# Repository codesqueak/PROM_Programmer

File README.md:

# PROM Programmer and Editor

PROM programmere for the following 32 x 8 PROM's

* National  74S188
* Fujitsu   7111
* Signetics 82S23
* AMD       27S18
* MMI       6330
* TI        18SA30
* Harris    7602

## Introduction

This board has been designed to allow the programming and editing of the above PROM's

* Programming timings as per the manufacturers recommendations
* All components are readily available from commercial component suppliers (..and eBay!)
* Copious test points
* Full documentation

For full documentation, see the [pdf here](PROM_Programmer.pdf)

* Yellow – Start
* Pink – Vcc
* Cyan – Programming Pulse
* Green – Chip Enable

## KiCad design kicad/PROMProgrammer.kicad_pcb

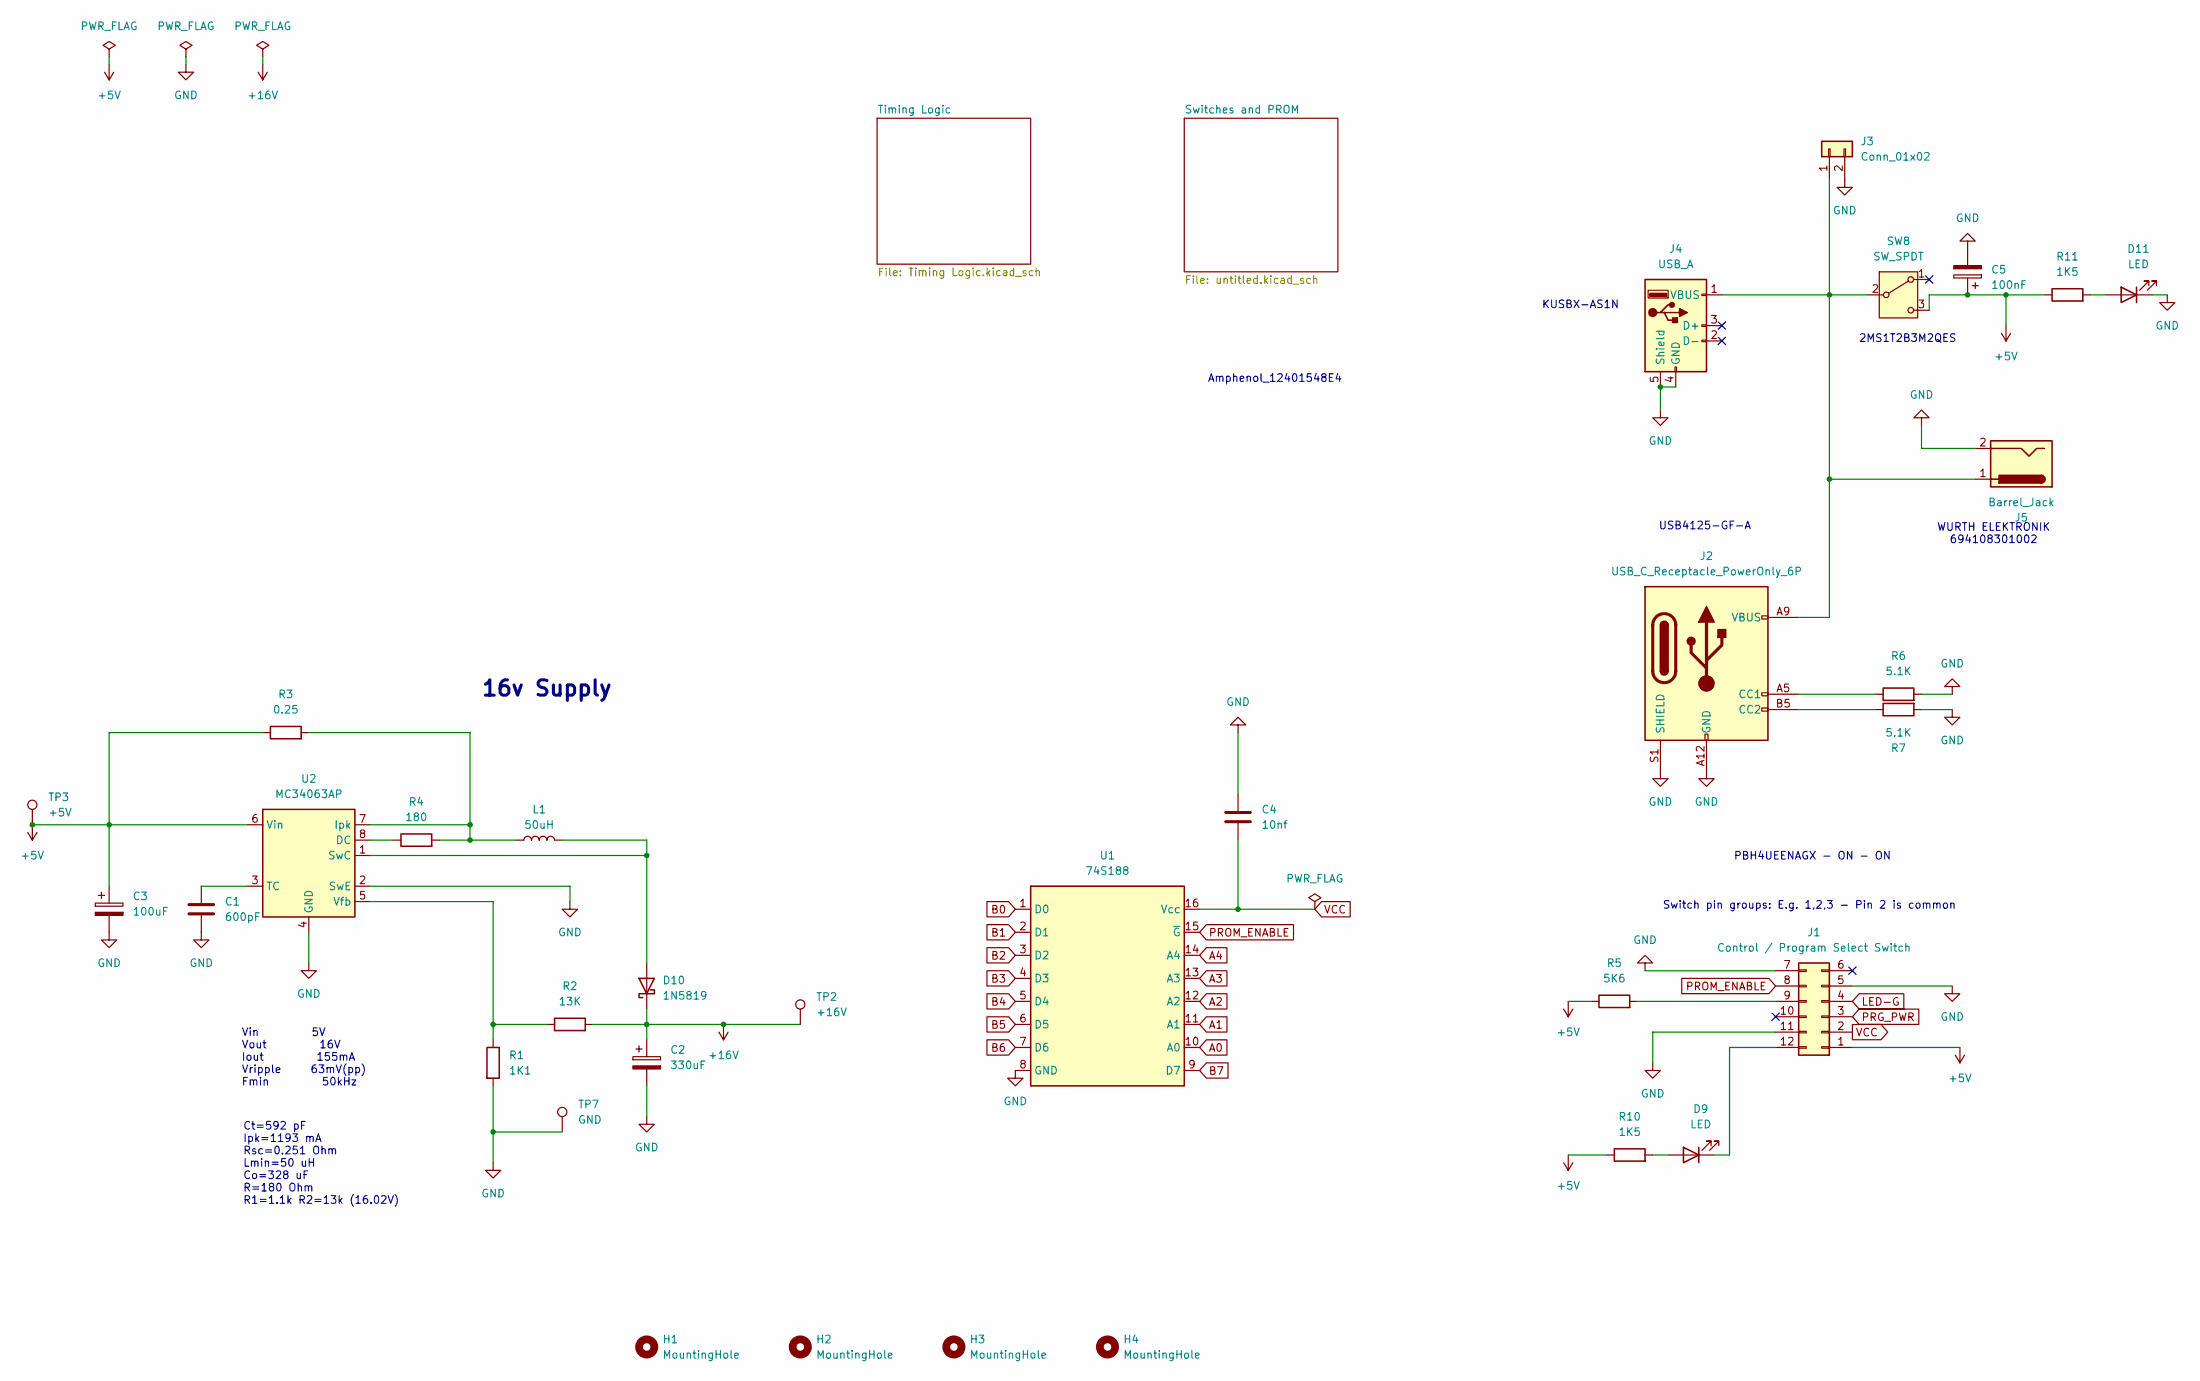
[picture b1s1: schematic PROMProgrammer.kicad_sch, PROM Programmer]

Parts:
C1: 600pF; C_Disc_D9.0mm_W2.5mm_P5.00mm
C2: 330uF; CP_Radial_D8.0mm_P3.50mm
C3: 100uF; CP_Radial_D5.0mm_P2.50mm
C4: 10nf; C_Disc_D6.0mm_W4.4mm_P5.00mm
C5: 100nF; CP_Radial_D5.0mm_P2.50mm
D9, D11: LED; LED_D3.0mm
D10: 1N5819; D_DO-41_SOD81_P10.16mm_Horizontal
H1, H2, H3, H4: MountingHole; MountingHole_3.2mm_M3_Pad
J1: Control / Program Select Switch; Push_Button_4PDT_2x06_P2.50mm_Vertical
J2: USB_C_Receptacle_PowerOnly_6P; USB_C_Receptacle_GCT_USB4125-xx-x-0190_6P_TopMnt_Horizontal
J3: Conn_01x02; Molex_KK-254_AE-6410-02A_1x02_P2.54mm_Vertical
J4: USB_A; USB_A_Kycon_KUSBX-AS1N-B_Horizontal
J5: Barrel_Jack; BarrelJack_Wuerth_6941xx301002
L1: 50uH; L_Radial_D7.8mm_P5.00mm_Fastron_07HCP
R1: 1K1; R_Axial_DIN0309_L9.0mm_D3.2mm_P12.70mm_Horizontal
R2: 13K; R_Axial_DIN0309_L9.0mm_D3.2mm_P12.70mm_Horizontal
R3: 0.25; R_Axial_DIN0309_L9.0mm_D3.2mm_P12.70mm_Horizontal
R4: 180; R_Axial_DIN0309_L9.0mm_D3.2mm_P12.70mm_Horizontal
R5: 5K6; R_Axial_DIN0309_L9.0mm_D3.2mm_P12.70mm_Horizontal
R6, R7: 5.1K; R_Axial_DIN0309_L9.0mm_D3.2mm_P12.70mm_Horizontal
R10, R11: 1K5; R_Axial_DIN0309_L9.0mm_D3.2mm_P12.70mm_Horizontal
SW8: SW_SPDT; PinHeader_1x03_P2.54mm_Vertical
TP2: +16V; TestPoint_THTPad_2.0x2.0mm_Drill1.0mm
TP3: +5V; TestPoint_THTPad_2.0x2.0mm_Drill1.0mm
TP7: GND; TestPoint_THTPad_2.0x2.0mm_Drill1.0mm
U1: 74S188; DIP_Socket-16_W4.3_W5.08_W7.62_W10.16_W10.9_3M_216-3340-00-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
U2: MC34063AP; DIP-8_W7.62mm

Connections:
+5V: C3.1, C5.1, J1.1, R3.1, R5.1, R10.1, R11.1, SW8.3 (C), TP3.1, U2.6 (Vin); also elsewhere on the board
+16V: C2.1, D10.1 (K), R2.2, TP2.1; also elsewhere on the board
A0: U1.10 (A0); also elsewhere on the board
A1: U1.11 (A1); also elsewhere on the board
A2: U1.12 (A2); also elsewhere on the board
A3: U1.13 (A3); also elsewhere on the board
A4: U1.14 (A4); also elsewhere on the board
B0: U1.1 (D0); also elsewhere on the board
B1: U1.2 (D1); also elsewhere on the board
B2: U1.3 (D2); also elsewhere on the board
B3: U1.4 (D3); also elsewhere on the board
B4: U1.5 (D4); also elsewhere on the board
B5: U1.6 (D5); also elsewhere on the board
B6: U1.7 (D6); also elsewhere on the board
B7: U1.9 (D7); also elsewhere on the board
GND: C1.2, C2.2, C3.2, C4.1, C5.2, D11.1 (K), J1.5, J1.7, J1.11, J2.A12 (GND), J2.B12 (GND), J2.S1 (SHIELD), J3.2, J4.4 (GND), J4.5 (Shield), J5.2, R1.2, R6.2, R7.2, TP7.1, U1.8 (GND), U2.2 (SwE), U2.4 (GND); also elsewhere on the board
LED-G: J1.4; also elsewhere on the board
unnamed: D9.2 (A), R10.2
unnamed: D9.1 (K), J1.12
unnamed: D10.2 (A), L1.2, U2.1 (SwC)
unnamed: D11.2 (A), R11.2
unnamed: J1.9, R5.2
unnamed: J2.A5 (CC1), R6.1
unnamed: J2.B5 (CC2), R7.1
unnamed: J2.A9 (VBUS), J2.B9 (VBUS), J3.1, J4.1 (VBUS), J5.1, SW8.2 (B)
unnamed: R4.1, U2.8 (DC)
unnamed: L1.1, R3.2, R4.2, U2.7 (Ipk)
unnamed: C1.1, U2.3 (TC)
unnamed: R1.1, R2.1, U2.5 (Vfb)
PRG_PWR: J1.3; also elsewhere on the board
PROM_ENABLE: J1.8, U1.15 (~G); also elsewhere on the board
VCC: C4.2, J1.2, U1.16 (Vcc)

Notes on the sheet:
Vin 5V Vout 16V Iout 155mA Vripple 63mV(pp) Fmin 50kHz
Switch pin groups: E.g. 1,2,3 - Pin 2 is common
Ct=592 pF Ipk=1193 mA Rsc=0.251 Ohm Lmin=50 uH Co=328 uF R=180 Ohm R1=1.1k R2=13k (16.02V)
KUSBX-AS1N
2MS1T2B3M2QES
16v Supply
PBH4UEENAGX - ON - ON
WURTH ELEKTRONIK 694108301002
USB4125-GF-A
Amphenol_12401548E4

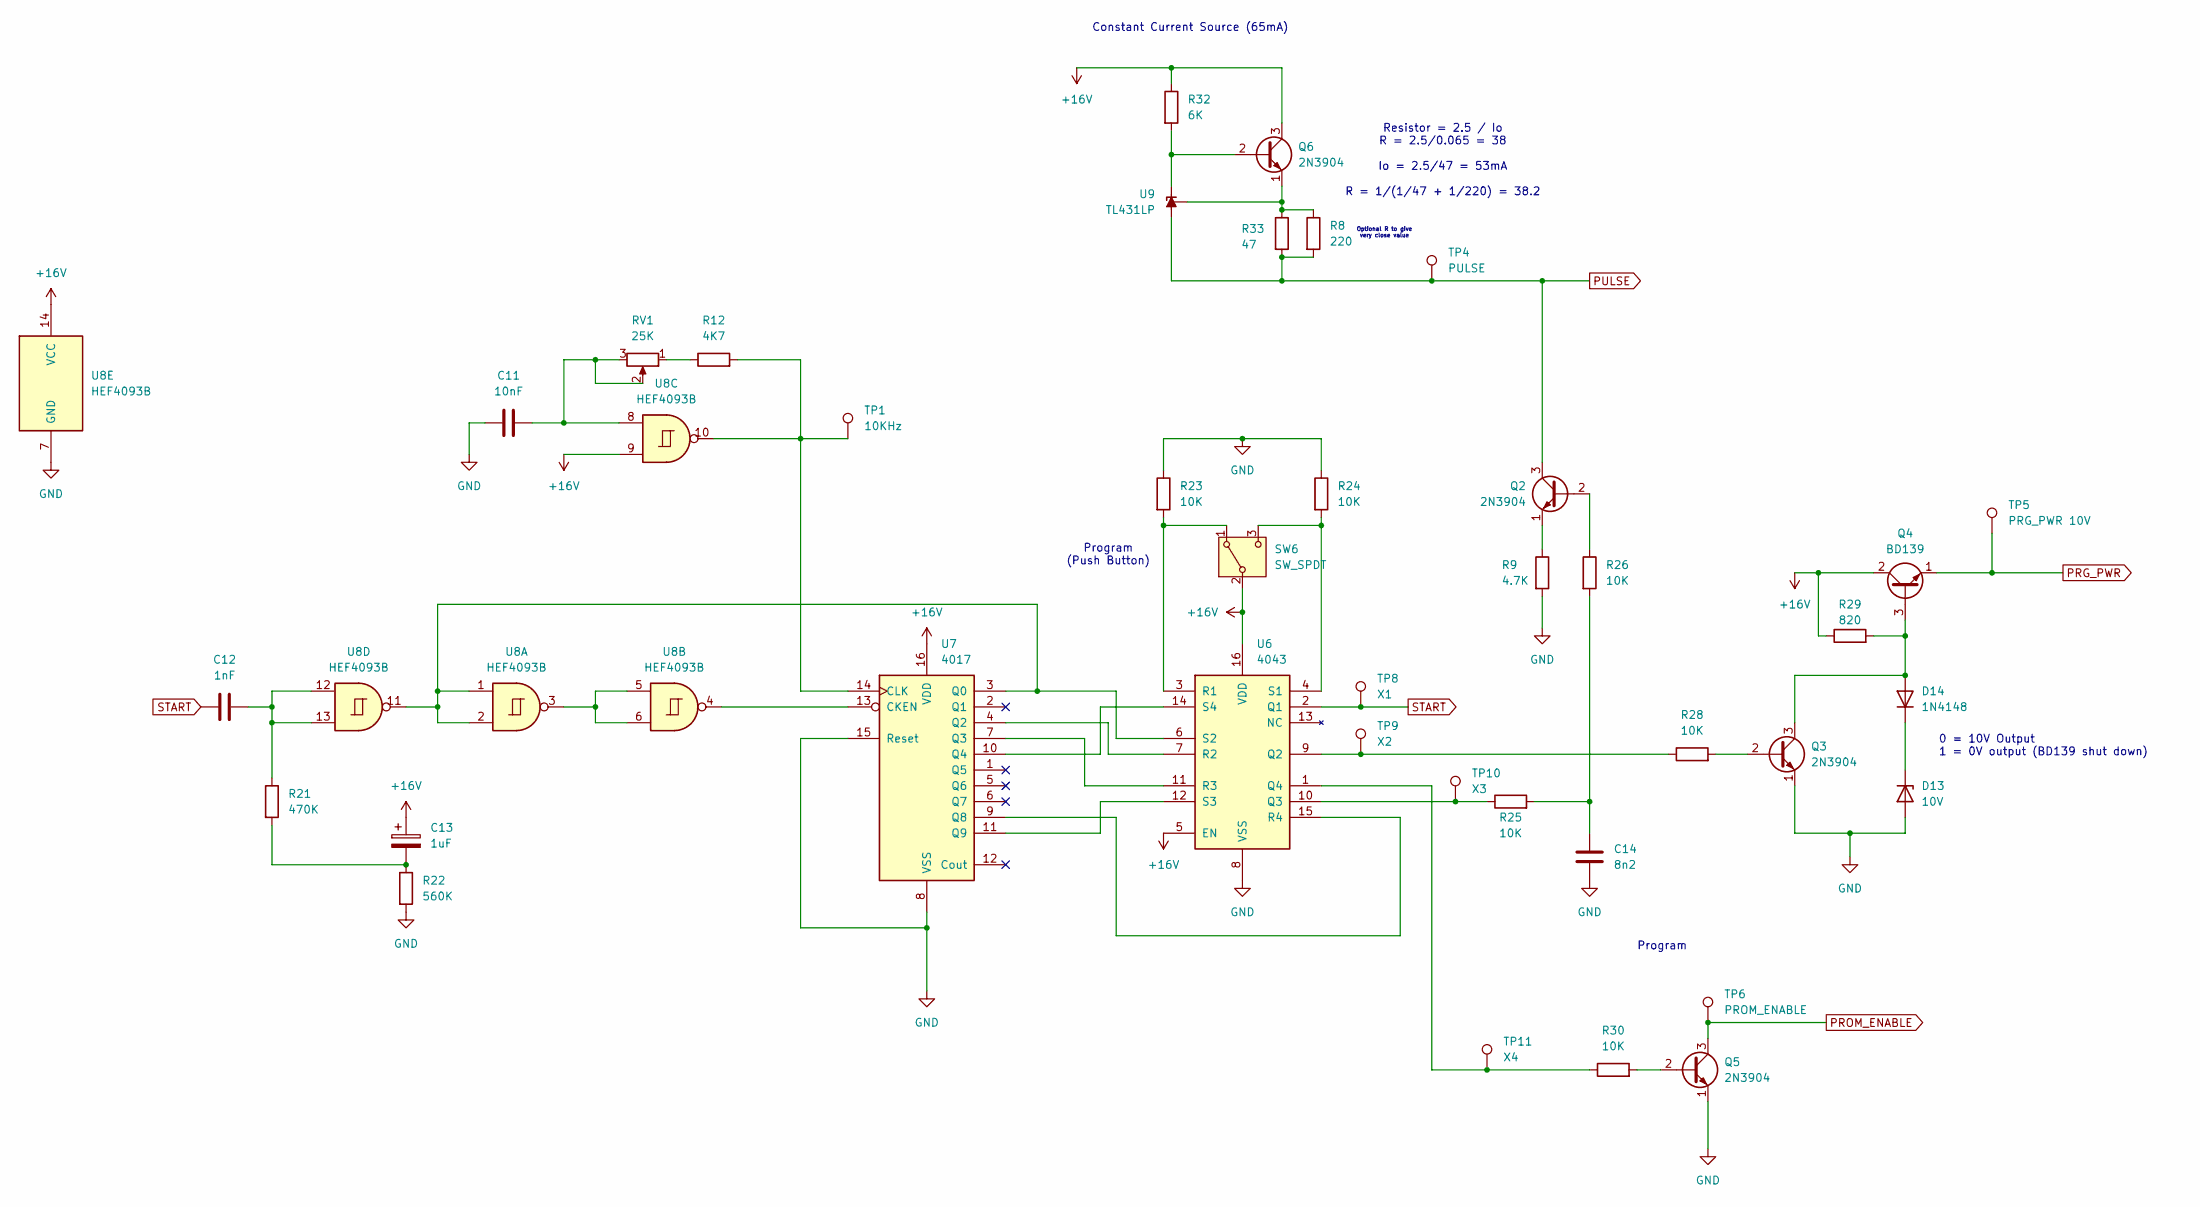
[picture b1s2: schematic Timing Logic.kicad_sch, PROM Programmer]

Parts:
C11: 10nF; C_Disc_D6.0mm_W4.4mm_P5.00mm
C12: 1nF; C_Disc_D6.0mm_W4.4mm_P5.00mm
C13: 1uF; CP_Radial_D4.0mm_P2.00mm
C14: 8n2; C_Disc_D6.0mm_W4.4mm_P5.00mm
D13: 10V; D_DO-41_SOD81_P12.70mm_Horizontal
D14: 1N4148; D_DO-35_SOD27_P7.62mm_Horizontal
Q2, Q3, Q5, Q6: 2N3904; TO-92_Inline
Q4: BD139; TO-126-3_Horizontal_TabDown
R8: 220; R_Axial_DIN0309_L9.0mm_D3.2mm_P12.70mm_Horizontal
R9: 4.7K; R_Axial_DIN0309_L9.0mm_D3.2mm_P12.70mm_Horizontal
R12: 4K7; R_Axial_DIN0309_L9.0mm_D3.2mm_P12.70mm_Horizontal
R21: 470K; R_Axial_DIN0309_L9.0mm_D3.2mm_P12.70mm_Horizontal
R22: 560K; R_Axial_DIN0309_L9.0mm_D3.2mm_P12.70mm_Horizontal
R23, R24, R25, R26, R28, R30: 10K; R_Axial_DIN0309_L9.0mm_D3.2mm_P12.70mm_Horizontal
R29: 820; R_Axial_DIN0309_L9.0mm_D3.2mm_P12.70mm_Horizontal
R32: 6K; R_Axial_DIN0309_L9.0mm_D3.2mm_P12.70mm_Horizontal
R33: 47; R_Axial_DIN0309_L9.0mm_D3.2mm_P12.70mm_Horizontal
RV1: 25K; Potentiometer_Vishay_43_Horizontal
SW6: SW_SPDT; SW_NKK_GW12LJP
TP1: 10KHz; TestPoint_THTPad_2.0x2.0mm_Drill1.0mm
TP4: PULSE; TestPoint_THTPad_2.0x2.0mm_Drill1.0mm
TP5: PRG_PWR 10V; TestPoint_THTPad_2.0x2.0mm_Drill1.0mm
TP6: PROM_ENABLE; TestPoint_THTPad_2.0x2.0mm_Drill1.0mm
TP8: X1; TestPoint_THTPad_2.0x2.0mm_Drill1.0mm
TP9: X2; TestPoint_THTPad_2.0x2.0mm_Drill1.0mm
TP10: X3; TestPoint_THTPad_2.0x2.0mm_Drill1.0mm
TP11: X4; TestPoint_THTPad_2.0x2.0mm_Drill1.0mm
U6: 4043; DIP-16_W7.62mm_Socket
U7: 4017; DIP-16_W7.62mm_Socket
U8: HEF4093B; DIP-14_W7.62mm_Socket
U9: TL431LP; TO-92_Inline

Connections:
+16V: C13.1, Q4.2 (C), Q6.3 (C), R29.1, R32.1, SW6.2 (B), U6.5 (EN), U6.16 (VDD), U7.16 (VDD), U8.9, U8.14 (VCC); also elsewhere on the board
GND: C11.1, C14.2, D13.2 (A), Q3.1 (E), Q5.1 (E), R9.2, R22.2, R23.1, R24.1, U6.8 (VSS), U7.8 (VSS), U7.15 (Reset), U8.7 (GND); also elsewhere on the board
unnamed: C11.2, RV1.2, RV1.3, U8.8
unnamed: C12.2, R21.1, U8.12, U8.13
unnamed: C13.2, R21.2, R22.1
unnamed: C14.1, R25.2, R26.2
unnamed: D13.1 (K), D14.1 (K)
unnamed: D14.2 (A), Q3.3 (C), Q4.3 (B), R29.2
unnamed: Q2.2 (B), R26.1
unnamed: Q2.1 (E), R9.1
unnamed: Q3.2 (B), R28.2
unnamed: Q5.2 (B), R30.2
unnamed: Q6.2 (B), R32.2, U9.3 (K)
unnamed: Q6.1 (E), R8.1, R33.1, U9.1 (REF)
unnamed: R12.1, RV1.1
unnamed: R23.2, SW6.1 (A), U6.3 (R1)
unnamed: R24.2, SW6.3 (C), U6.4 (S1)
unnamed: R28.1, TP9.1, U6.9 (Q2)
unnamed: R25.1, TP10.1, U6.10 (Q3)
unnamed: R30.1, TP11.1, U6.1 (Q4)
unnamed: U6.7 (R2), U7.4 (Q2)
unnamed: U6.11 (R3), U7.7 (Q3)
unnamed: U6.15 (R4), U7.9 (Q8)
unnamed: U6.6 (S2), U7.3 (Q0), U8.1, U8.2, U8.11
unnamed: U6.12 (S3), U7.11 (Q9)
unnamed: U6.14 (S4), U7.10 (Q4)
unnamed: U7.13 (CKEN), U8.4
unnamed: R12.2, TP1.1, U7.14 (CLK), U8.10
unnamed: U8.3, U8.5, U8.6
PRG_PWR: Q4.1 (E), TP5.1; also elsewhere on the board
PROM_ENABLE: Q5.3 (C), TP6.1; also elsewhere on the board
PULSE: Q2.3 (C), R8.2, R33.2, TP4.1, U9.2 (A); also elsewhere on the board
START: C12.1, TP8.1, U6.2 (Q1)

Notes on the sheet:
Program (Push Button)
Program
Constant Current Source (65mA)
Resistor = 2.5 / Io R = 2.5/0.065 = 38 Io = 2.5/47 = 53mA R = 1/(1/47 + 1/220) = 38.2
Optional R to give very close value
0 = 10V Output 1 = 0V output (BD139 shut down)

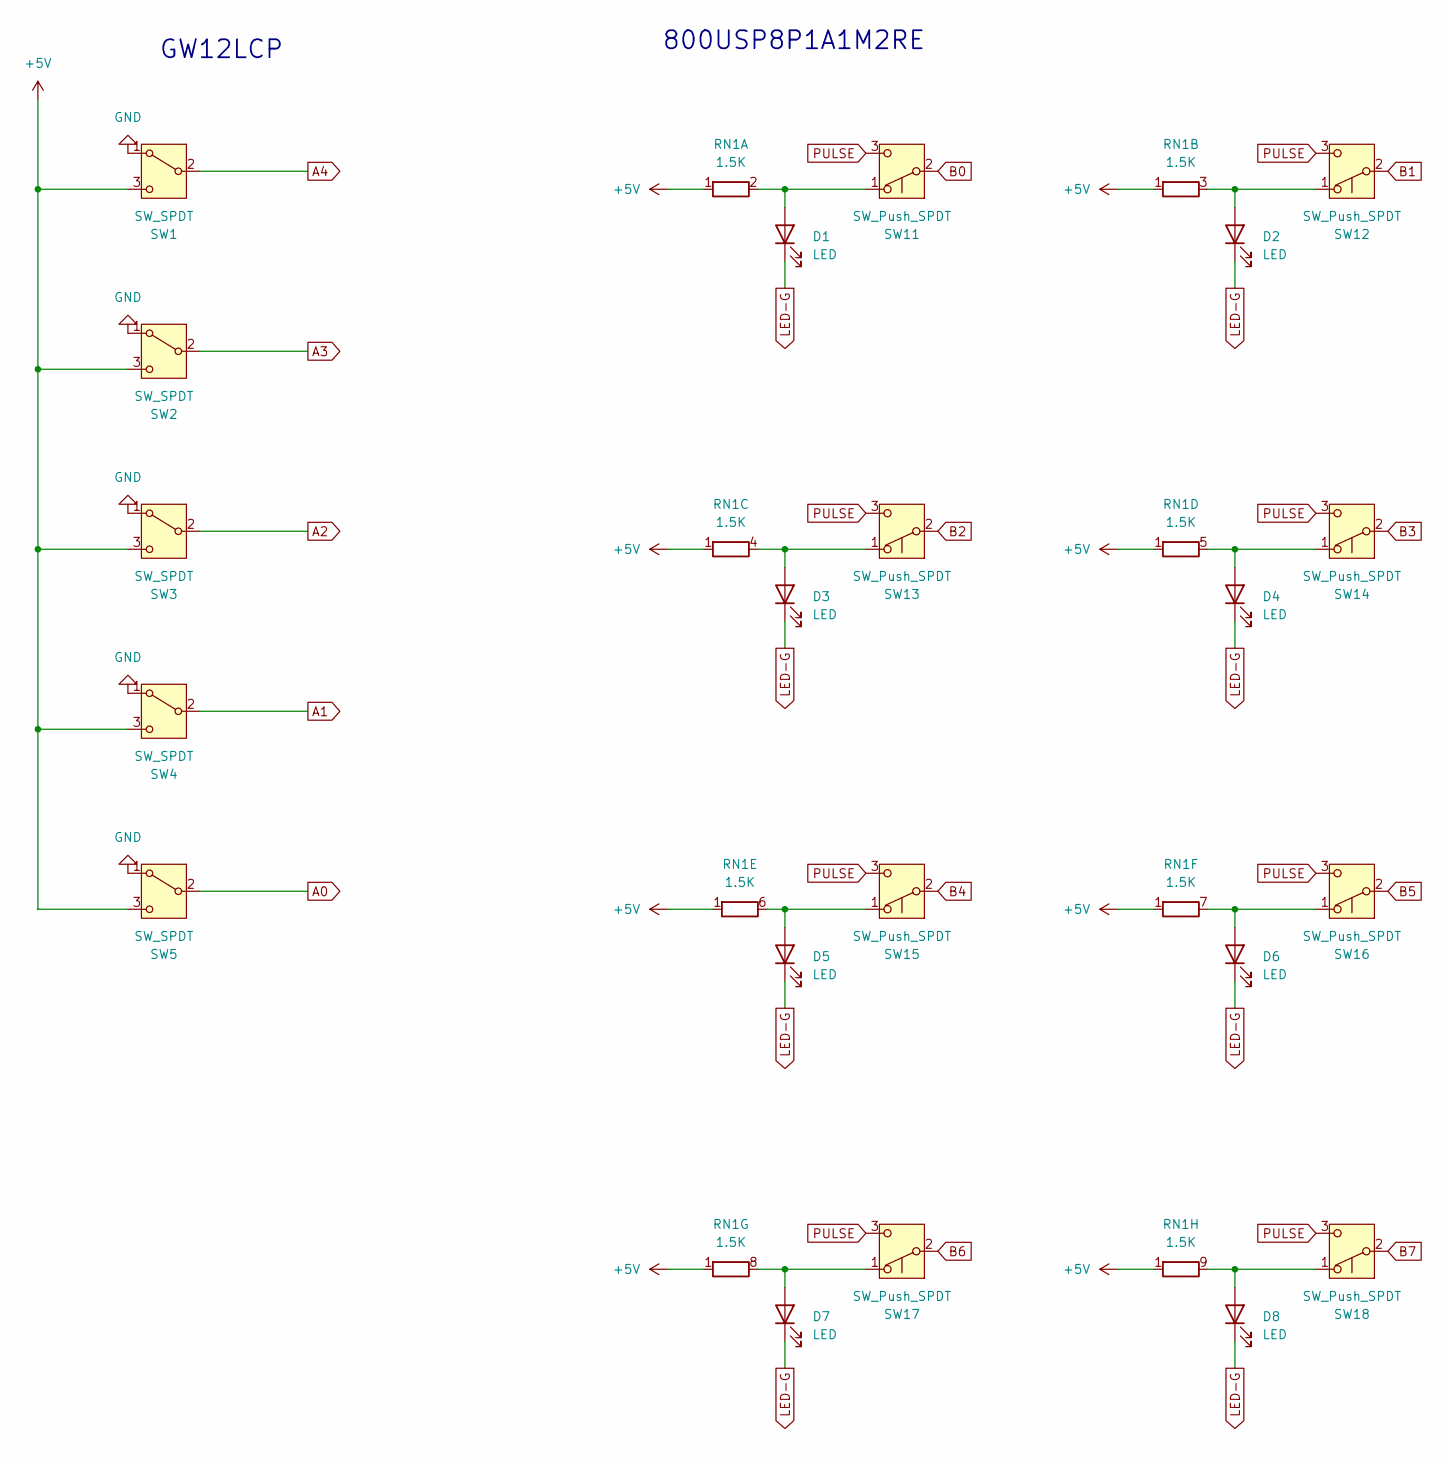
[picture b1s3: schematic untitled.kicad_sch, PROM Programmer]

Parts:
D1, D2, D3, D4, D5, D6, D7, D8: LED; LED_D3.0mm
RN1: 1.5K; R_Array_SIP9
SW1, SW2, SW3, SW4, SW5: SW_SPDT; SW_NKK_GW12LJP
SW11, SW12, SW13, SW14, SW15, SW16, SW17, SW18: SW_Push_SPDT; SW_NKK_GW12LJP

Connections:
+5V: RN1.1 (R1), SW1.3 (C), SW2.3 (C), SW3.3 (C), SW4.3 (C), SW5.3 (C); also elsewhere on the board
A0: SW5.2 (B); also elsewhere on the board
A1: SW4.2 (B); also elsewhere on the board
A2: SW3.2 (B); also elsewhere on the board
A3: SW2.2 (B); also elsewhere on the board
A4: SW1.2 (B); also elsewhere on the board
B0: SW11.2 (B); also elsewhere on the board
B1: SW12.2 (B); also elsewhere on the board
B2: SW13.2 (B); also elsewhere on the board
B3: SW14.2 (B); also elsewhere on the board
B4: SW15.2 (B); also elsewhere on the board
B5: SW16.2 (B); also elsewhere on the board
B6: SW17.2 (B); also elsewhere on the board
B7: SW18.2 (B); also elsewhere on the board
GND: SW1.1 (A), SW2.1 (A), SW3.1 (A), SW4.1 (A), SW5.1 (A); also elsewhere on the board
LED-G: D1.1 (K), D2.1 (K), D3.1 (K), D4.1 (K), D5.1 (K), D6.1 (K), D7.1 (K), D8.1 (K); also elsewhere on the board
unnamed: D1.2 (A), RN1.2 (R1.2), SW11.1 (A)
unnamed: D2.2 (A), RN1.3 (R2.2), SW12.1 (A)
unnamed: D3.2 (A), RN1.4 (R3.2), SW13.1 (A)
unnamed: D4.2 (A), RN1.5 (R4.2), SW14.1 (A)
unnamed: D5.2 (A), RN1.6 (R5.2), SW15.1 (A)
unnamed: D6.2 (A), RN1.7 (R6.2), SW16.1 (A)
unnamed: D7.2 (A), RN1.8 (R7.2), SW17.1 (A)
unnamed: D8.2 (A), RN1.9 (R8.2), SW18.1 (A)
PULSE: SW11.3 (C), SW12.3 (C), SW13.3 (C), SW14.3 (C), SW15.3 (C), SW16.3 (C), SW17.3 (C), SW18.3 (C); also elsewhere on the board

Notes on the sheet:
800USP8P1A1M2RE
GW12LCP

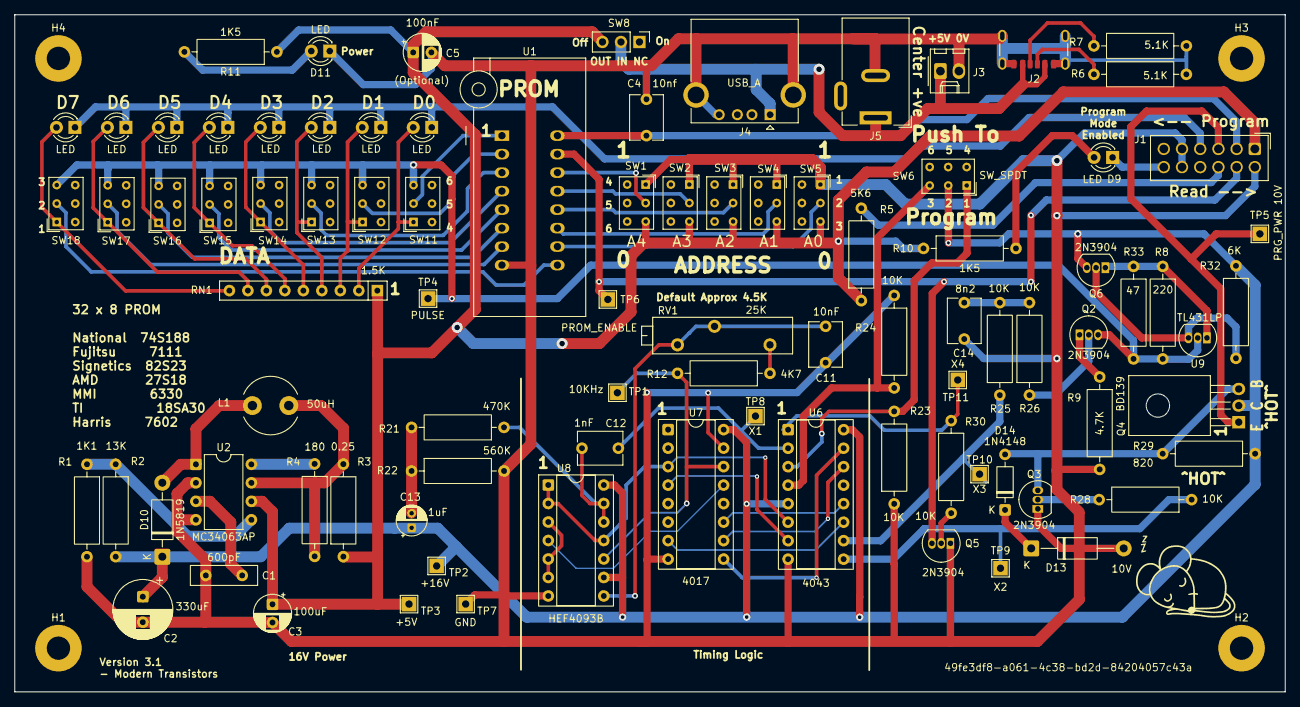
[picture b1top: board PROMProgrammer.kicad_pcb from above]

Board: 2 copper layers, 174.5 x 93.0 mm, 97 parts (1 on the bottom side), 69 nets.

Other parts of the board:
G001: LOGO; sleepymouse_very_small
G002: LOGO; sleepymouse_very_small_back
G003: LOGO; qr_code

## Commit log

2025-03-22 Initial upload
2025-03-22 docs
2025-03-22 Add timings
2025-03-23 Tweak docs
2025-04-01 Starting docs
2025-04-06 Version update
2025-04-16 Update docs
2025-04-24 Tidy up & docs
2025-05-27 Minor layout changes
2025-08-03 Tweak layout, add part silkscreen values
2025-08-10 Update transistors
2025-09-21 All working and tidy
